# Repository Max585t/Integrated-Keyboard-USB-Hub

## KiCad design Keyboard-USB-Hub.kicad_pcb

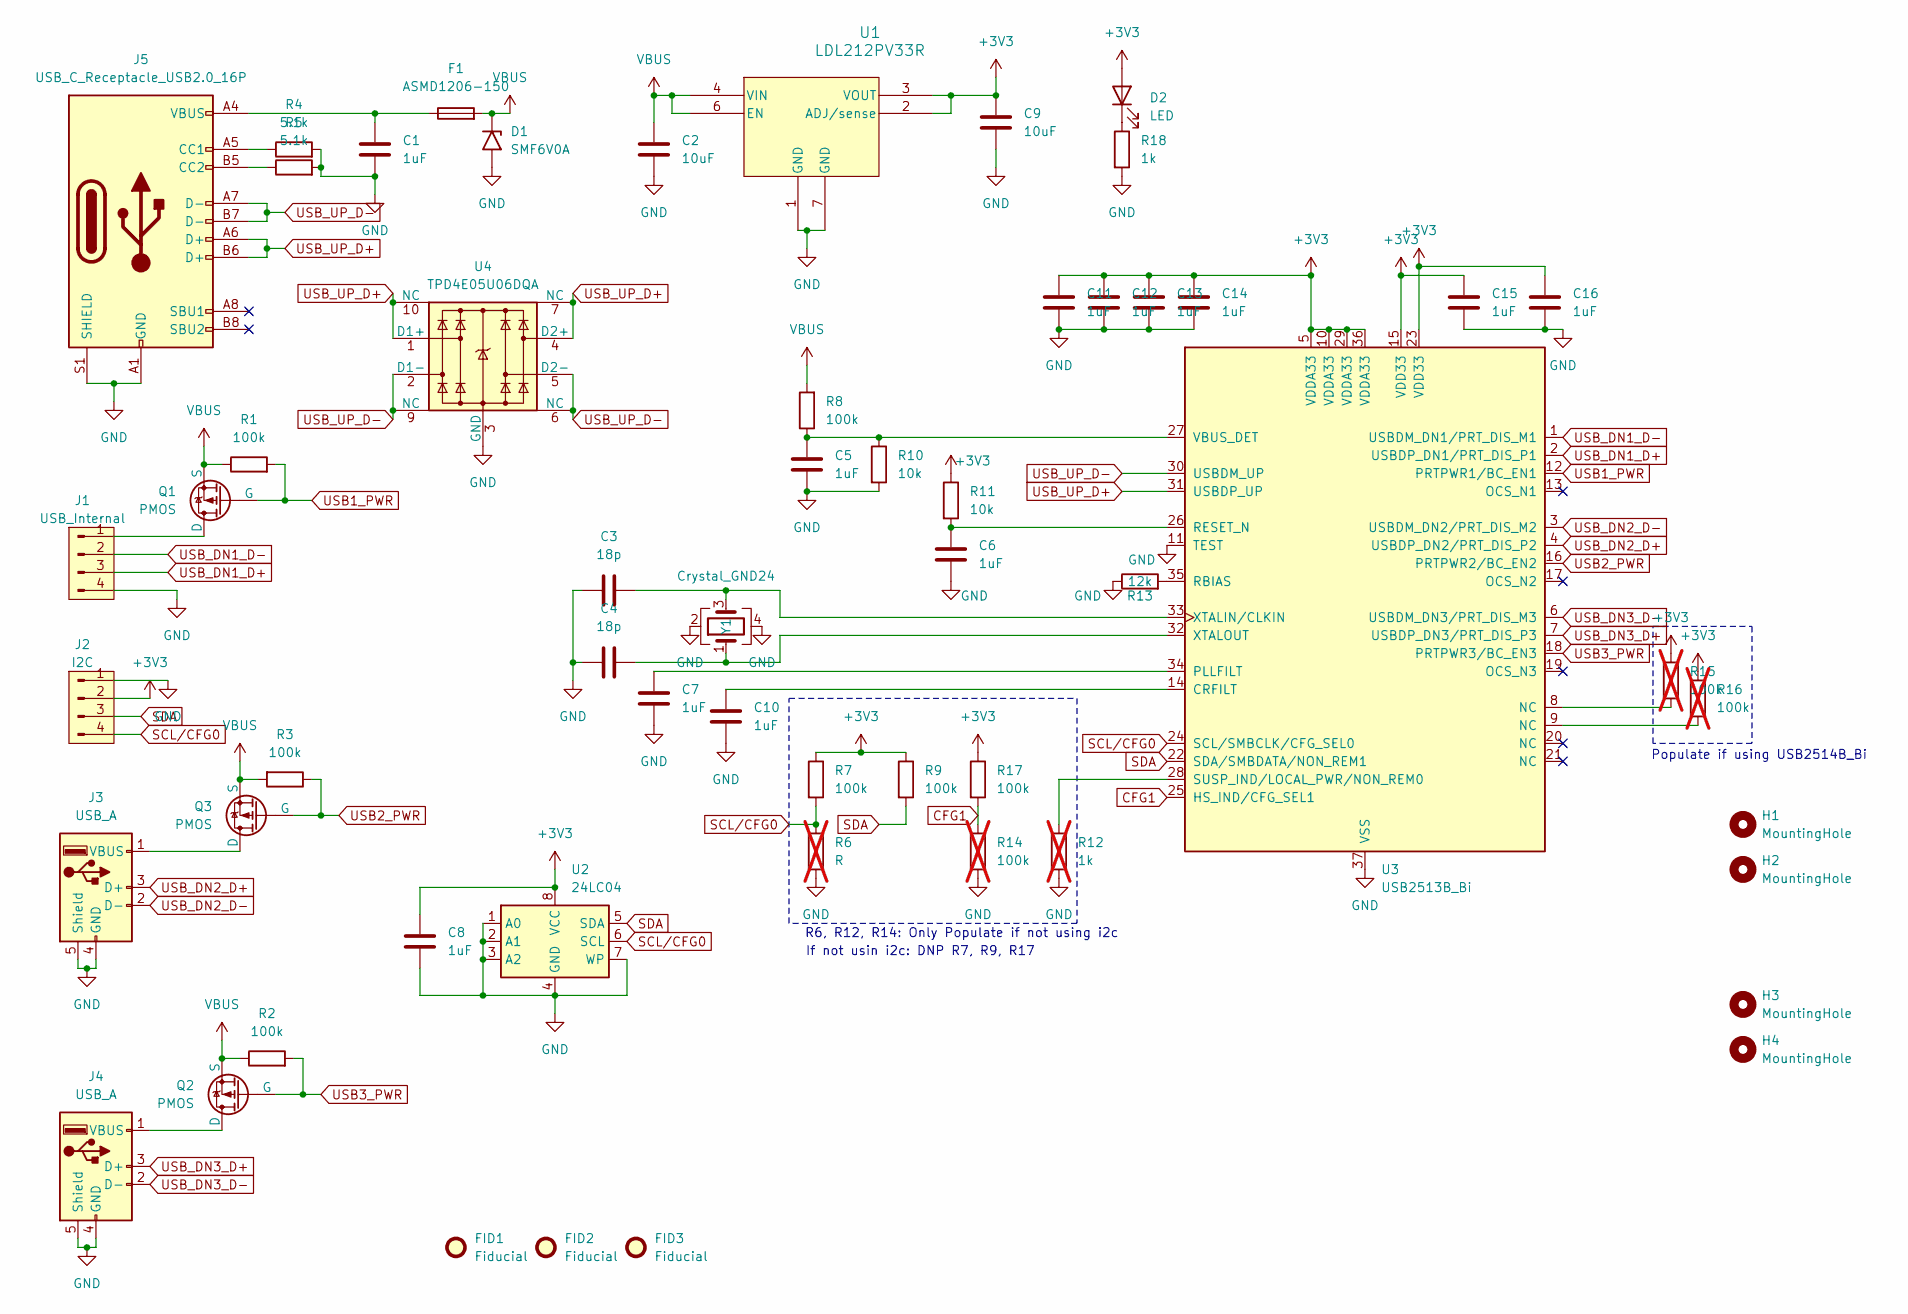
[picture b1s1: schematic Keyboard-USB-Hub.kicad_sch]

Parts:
C1, C5, C6, C7, C8, C10, C11, C12, C13, C14, C15, C16: 1uF; C_0402_1005Metric
C2, C9: 10uF; C_0402_1005Metric
C3, C4: 18p; C_0402_1005Metric
D1: SMF6V0A; D_SMF
D2: LED; LED_0603_1608Metric
F1: ASMD1206-150; Fuse_1206_3216Metric
FID1, FID2, FID3: Fiducial; Fiducial_0.5mm_Mask1mm
H1, H2, H3, H4: MountingHole; MountingHole_2.2mm_M2_ISO14580
J1: USB_Internal; JST_SH_SM04B-SRSS-TB_1x04-1MP_P1.00mm_Horizontal
J2: I2C; JST_SH_SM04B-SRSS-TB_1x04-1MP_P1.00mm_Horizontal
J3, J4: USB_A; GCT_USB1015
J5: USB_C_Receptacle_USB2.0_16P; USB_C_Receptacle_GCT_USB4105-xx-A_16P_TopMnt_Horizontal
Q1, Q2, Q3: PMOS; SOT-23
R1, R2, R3, R7, R8, R9, R17: 100k; R_0402_1005Metric
R4, R5: 5.1k; R_0402_1005Metric
R6: R; R_0402_1005Metric; not fitted
R10, R11: 10k; R_0402_1005Metric
R12: 1k; R_0402_1005Metric; not fitted
R13: 12k; R_0402_1005Metric
R14, R15, R16: 100k; R_0402_1005Metric; not fitted
R18: 1k; R_0402_1005Metric
U1: LDL212PV33R; DFN-6-1EP_2x2mm_P0.65mm_EP1x1.6mm
U2: 24LC04; DFN-8-1EP_3x2mm_P0.5mm_EP1.7x1.4mm
U3: USB2513B_Bi; QFN-36-1EP_6x6mm_P0.5mm_EP3.7x3.7mm
U4: TPD4E05U06DQA; USON-10_2.5x1.0mm_P0.5mm
Y1: Crystal_GND24; Crystal_SMD_Abracon_ABM8G-4Pin_3.2x2.5mm

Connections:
+3V3: C8.1, C9.1, C11.1, C12.1, C13.1, C14.1, C15.1, C16.1, D2.2 (A), J2.2, R7.1, R9.1, R11.1, R15.2, R16.1, R17.1, U1.2 (ADJ/sense), U1.3 (VOUT), U2.8 (VCC), U3.5 (VDDA33), U3.10 (VDDA33), U3.15 (VDD33), U3.23 (VDD33), U3.29 (VDDA33), U3.36 (VDDA33)
CFG1: R14.1, R17.2, U3.25 (HS_IND/CFG_SEL1)
GND: C1.2, C2.2, C3.1, C4.1, C5.2, C6.2, C7.2, C8.2, C9.2, C10.2, C11.2, C12.2, C13.2, C14.2, C15.2, C16.2, D1.2 (A2), J1.4, J2.1, J3.4 (GND), J3.5 (Shield), J4.4 (GND), J4.5 (Shield), J5.A1 (GND), J5.A12 (GND), J5.B1 (GND), J5.B12 (GND), J5.S1 (SHIELD), R4.2, R5.2, R6.2, R10.2, R12.2, R13.1, R14.2, R18.2, U1.1 (GND), U1.7 (GND), U2.1 (A0), U2.2 (A1), U2.3 (A2), U2.4 (GND), U2.7 (WP), U2.9 (EP), U3.11 (TEST), U3.37 (VSS), U4.3 (GND), U4.8 (GND), Y1.2, Y1.4
unnamed: C1.1, F1.1, J5.A4 (VBUS), J5.A9 (VBUS), J5.B4 (VBUS), J5.B9 (VBUS)
unnamed: D2.1 (K), R18.1
unnamed: J1.1, Q1.1 (D)
unnamed: J3.1 (VBUS), Q3.1 (D)
unnamed: J4.1 (VBUS), Q2.1 (D)
unnamed: J5.A5 (CC1), R4.1
unnamed: J5.B5 (CC2), R5.1
unnamed: R15.1, U3.8 (NC)
unnamed: R16.2, U3.9 (NC)
unnamed: C10.1, U3.14 (CRFILT)
unnamed: C7.1, U3.34 (PLLFILT)
unnamed: R13.2, U3.35 (RBIAS)
unnamed: C6.1, R11.2, U3.26 (RESET_N)
unnamed: R12.1, U3.28 (SUSP_IND/LOCAL_PWR/NON_REM0)
unnamed: C5.1, R8.1, R10.1, U3.27 (VBUS_DET)
unnamed: C3.2, U3.33 (XTALIN/CLKIN), Y1.3
unnamed: C4.2, U3.32 (XTALOUT), Y1.1
SCL/CFG0: J2.4, R6.1, R7.2, U2.6 (SCL), U3.24 (SCL/SMBCLK/CFG_SEL0)
SDA: J2.3, R9.2, U2.5 (SDA), U3.22 (SDA/SMBDATA/NON_REM1)
USB1_PWR: Q1.2 (G), R1.2, U3.12 (PRTPWR1/BC_EN1)
USB2_PWR: Q3.2 (G), R3.1, U3.16 (PRTPWR2/BC_EN2)
USB3_PWR: Q2.2 (G), R2.2, U3.18 (PRTPWR3/BC_EN3)
USB_DN1_D+: J1.3, U3.2 (USBDP_DN1/PRT_DIS_P1)
USB_DN1_D-: J1.2, U3.1 (USBDM_DN1/PRT_DIS_M1)
USB_DN2_D+: J3.3 (D+), U3.4 (USBDP_DN2/PRT_DIS_P2)
USB_DN2_D-: J3.2 (D-), U3.3 (USBDM_DN2/PRT_DIS_M2)
USB_DN3_D+: J4.3 (D+), U3.7 (USBDP_DN3/PRT_DIS_P3)
USB_DN3_D-: J4.2 (D-), U3.6 (USBDM_DN3/PRT_DIS_M3)
USB_UP_D+: J5.A6 (D+), J5.B6 (D+), U3.31 (USBDP_UP), U4.1 (D1+), U4.4 (D2+), U4.7 (NC), U4.10 (NC)
USB_UP_D-: J5.A7 (D-), J5.B7 (D-), U3.30 (USBDM_UP), U4.2 (D1-), U4.5 (D2-), U4.6 (NC), U4.9 (NC)
VBUS: C2.1, D1.1 (A1), F1.2, Q1.3 (S), Q2.3 (S), Q3.3 (S), R1.1, R2.1, R3.2, R8.2, U1.4 (VIN), U1.6 (EN)

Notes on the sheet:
If not usin i2c: DNP R7, R9, R17
R6, R12, R14: Only Populate if not using i2c
Populate if using USB2514B_Bi

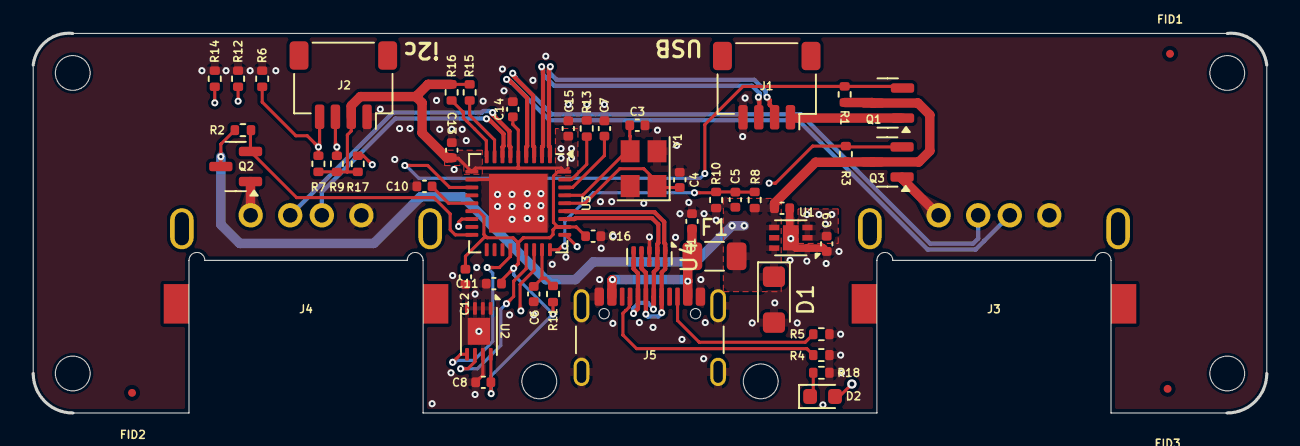
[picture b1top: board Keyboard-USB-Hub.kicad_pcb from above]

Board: 4 copper layers, 78.0 x 24.0 mm, 59 parts (0 on the bottom side), 34 nets.

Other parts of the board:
H7, H8: MountingHole; MountingHole_2.2mm_M2_ISO14580

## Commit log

2025-11-10 Add LED
